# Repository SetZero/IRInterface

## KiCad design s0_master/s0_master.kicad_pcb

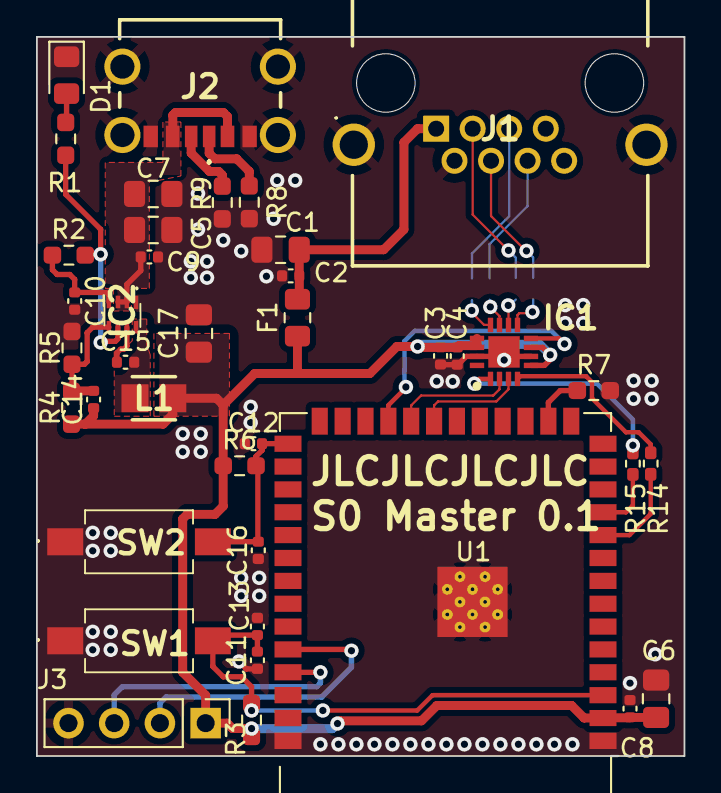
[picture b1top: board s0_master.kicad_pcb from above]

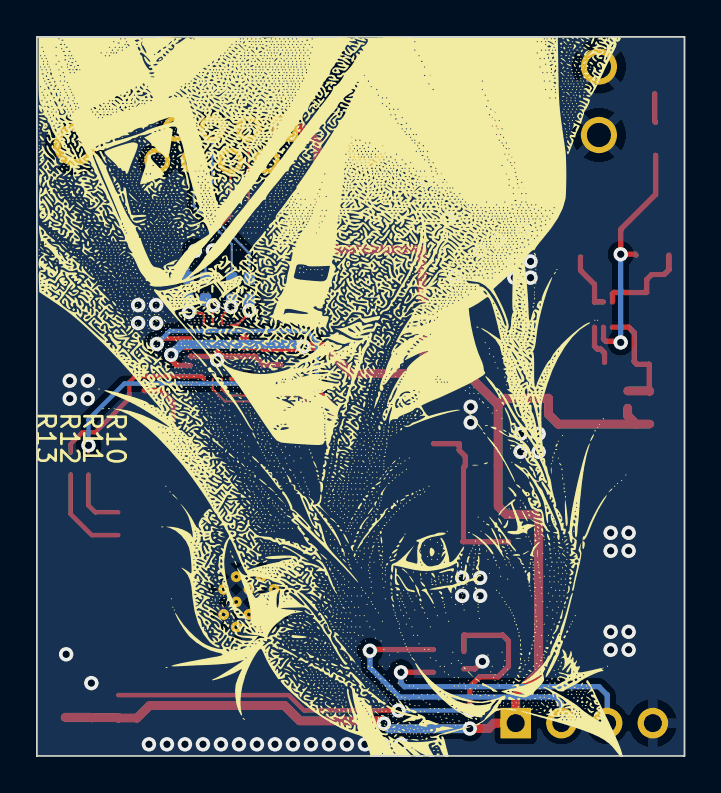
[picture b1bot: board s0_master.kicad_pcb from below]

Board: 2 copper layers, 36.0 x 40.0 mm, 43 parts (4 on the bottom side), 32 nets.

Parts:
C1: 100u; C_0805_2012Metric_Pad1.18x1.45mm_HandSolder
C2, C3, C4: 1u; C_0402_1005Metric
C5, C7: 10uF; C_0805_2012Metric_Pad1.18x1.45mm_HandSolder
C6, C17: 22uF; C_0805_2012Metric_Pad1.18x1.45mm_HandSolder
C8, C9, C11, C12, C13, C15, C16: 0.1uF; C_0402_1005Metric
C10: 1uF; C_0402_1005Metric
C14: 22pF; C_0402_1005Metric
D1: LED_Small; LED_0805_2012Metric_Pad1.15x1.40mm_HandSolder
F1: 1A; Fuse_0805_2012Metric_Pad1.15x1.40mm_HandSolder
IC1: THVD1424RGTR; QFN50P300X300X100-17N-D
IC2: MP2322GQH-Z; MP2322GQHZ
J1: RJHSE5E80
J2: 217175-0001; 2171750001
J3: DEBUG; PinHeader_1x04_P2.54mm_Vertical
L1: 3.3uH; INDPM2424X100N
R1: 75R; R_0603_1608Metric_Pad0.98x0.95mm_HandSolder
R2: 100k; R_0603_1608Metric_Pad0.98x0.95mm_HandSolder
R3, R6, R8, R9: 10k; R_0603_1608Metric_Pad0.98x0.95mm_HandSolder
R4: 976k; R_0603_1608Metric_Pad0.98x0.95mm_HandSolder
R5: 220k; R_0603_1608Metric_Pad0.98x0.95mm_HandSolder
R7: 2k; R_0603_1608Metric_Pad0.98x0.95mm_HandSolder
R10, R11, R12, R13, R14, R15: 0R; R_0402_1005Metric_Pad0.72x0.64mm_HandSolder
SW1, SW2: SW_Omron_B3FS; PTS636SP50SMTRLFS
U1: ESP32-S3-WROOM-1

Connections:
+3V3: C3.1, C4.1, C6.2, C8.2, C14.1, C17.1, F1.1, IC1.5 (TERM_TX), IC1.7 (TERM_RX), IC1.13 (VIO), IC1.14 (VCC), J3.1, L1.2, R3.1, R4.1, R6.1, U1.2 (3V3)
+5V: C5.1, C7.1, C9.1, IC2.2 (IN), IC2.3 (EN), J2.A9 (VBUS_1), J2.B9 (VBUS_2)
BOOT: C12.2, C16.2, R6.2, SW2.2, U1.27 (GPIO0/BOOT)
DI+: J1.4, R13.1
DI-: J1.3, R12.2
DO+: J1.5, R10.2
DO-: J1.6, R11.2
EN: C11.2, C13.2, R3.2, SW1.2, U1.3 (EN)
GND: C1.2, C2.2, C3.2, C4.2, C5.2, C6.1, C7.2, C8.1, C9.2, C10.2, C11.1, C12.1, C13.1, C16.1, C17.2, D1.1 (K), IC1.6 (GND), IC1.15 (H/~F), IC1.17 (EP), IC2.1 (GND), J1.2, J1.MH1, J1.MH2, J2.A12 (GND_1), J2.B12 (GND_2), J2.MH1, J2.MH2, J2.MH3, J2.MH4, J3.4, R5.2, R7.2, R8.2, R9.2, SW1.1, SW2.1, U1.1 (GND), U1.40 (GND), U1.41 (GND)
GPIO46: R7.1, U1.16 (GPIO46)
unnamed: D1.2 (A), R1.2
unnamed: IC1.12 (A), R10.1
unnamed: IC1.11 (B), R11.1
unnamed: IC1.4 (D), R14.2
unnamed: IC1.1 (R), R15.1
unnamed: IC1.9 (Y), R13.2
unnamed: IC1.10 (Z), R12.1
unnamed: C15.1, IC2.7 (BST)
unnamed: C14.2, IC2.5 (FB), R4.2, R5.1
unnamed: IC2.6 (PG), R1.1, R2.2
unnamed: C15.2, IC2.8 (SW), L1.1
unnamed: C10.1, IC2.4 (VCC), R2.1
unnamed: J2.A5 (CC1), R8.1
unnamed: J2.B5 (CC2), R9.1
RXD0: J3.2, U1.36 (U0RXD/GPIO44/CLK_OUT2)
SLR: IC1.8 (SLR), U1.23 (GPIO21)
TXD0: J3.3, U1.37 (U0TXD/GPIO43/CLK_OUT1)
UART2_DE: IC1.3 (DE), U1.21 (GPIO13/TOUCH13/ADC2_CH2/FSPIQ/FSPIIO7/S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)
UART2_RE: IC1.2 (~RE), U1.22 (GPIO14/TOUCH14/ADC2_CH3/FSPIWP/FSPIDQS/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)
UART2_RX: R15.2, U1.11 (GPIO18/U1RXD/ADC2_CH7/CLK_OUT3)
UART2_TX: R14.1, U1.10 (GPIO17/U1TXD/ADC2_CH6)
VIN: C1.1, C2.1, F1.2, J1.1

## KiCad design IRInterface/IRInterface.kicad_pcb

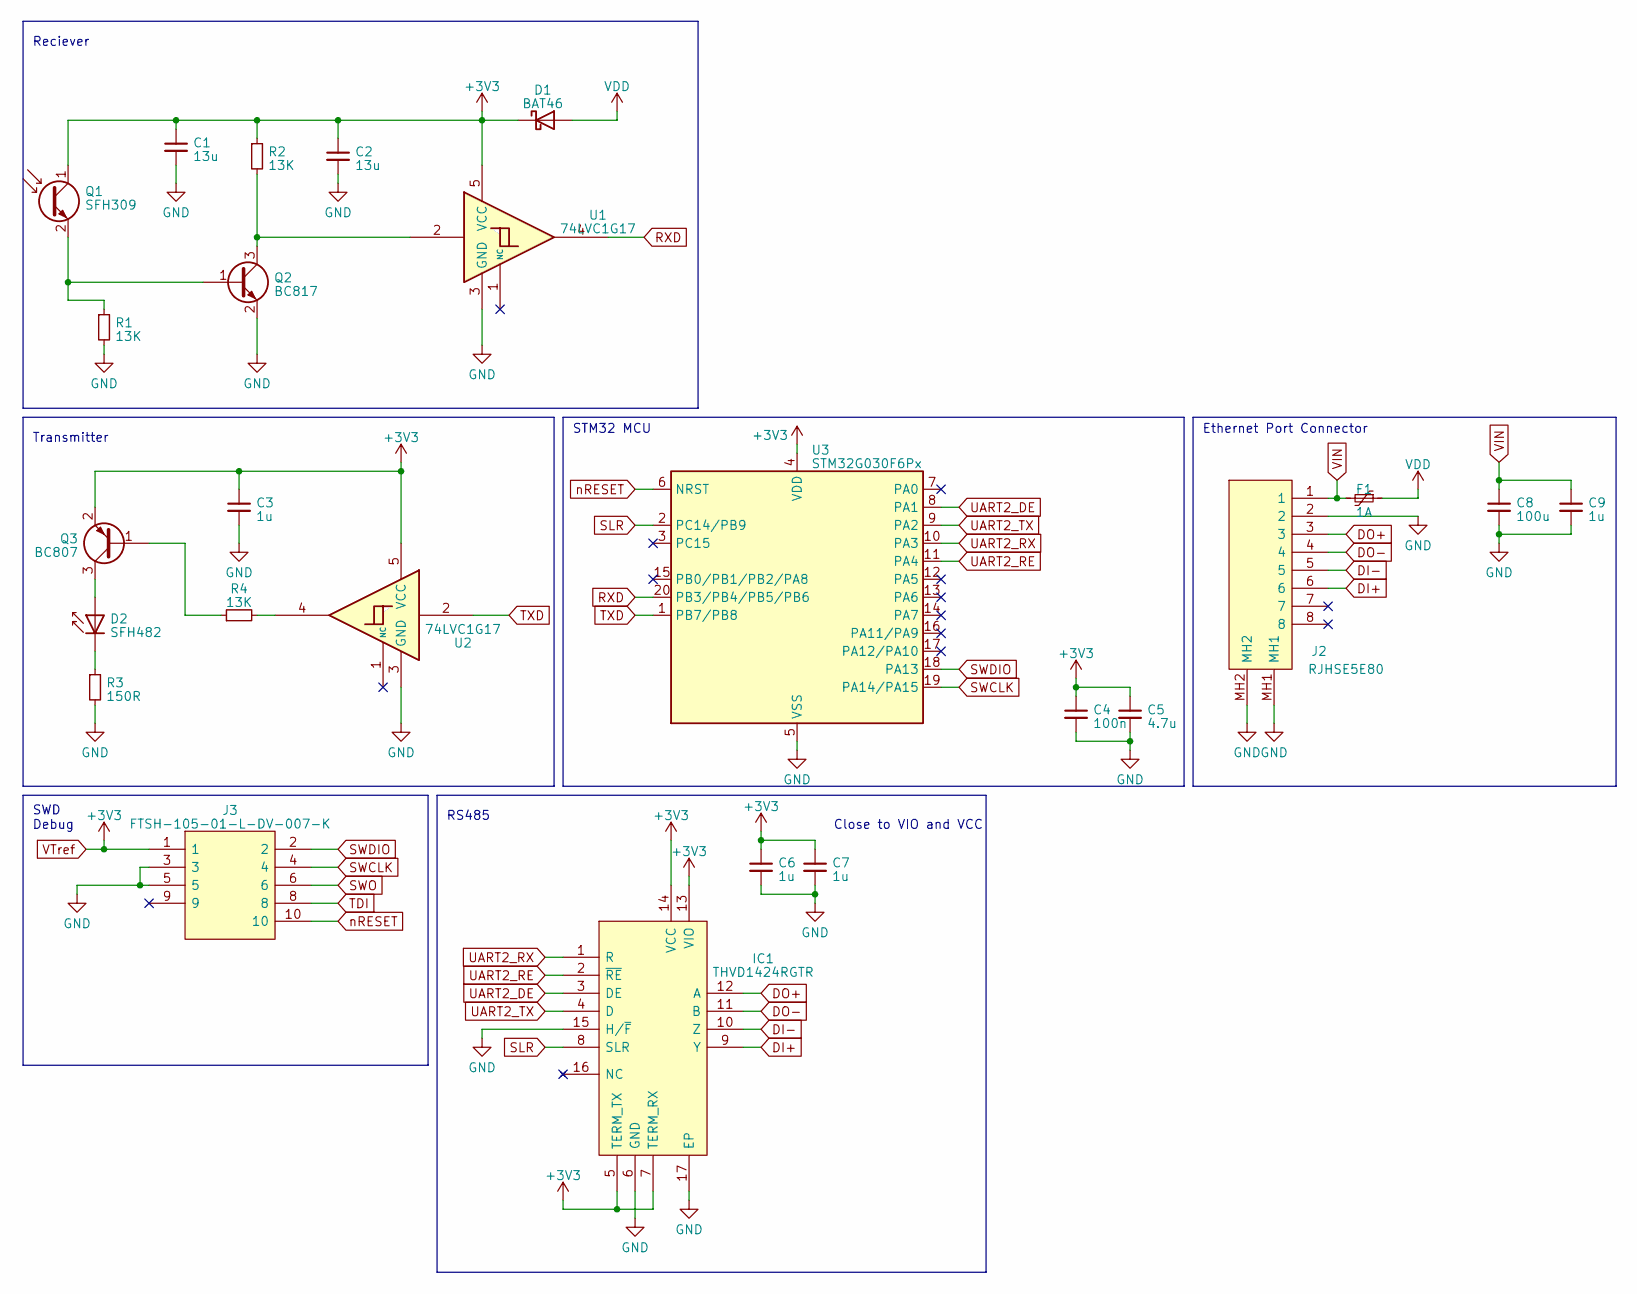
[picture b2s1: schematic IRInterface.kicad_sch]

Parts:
C1, C2: 13u; C_0402_1005Metric
C3, C6, C7, C9: 1u; C_0402_1005Metric
C4: 100n; C_0402_1005Metric
C5: 4.7u; C_0402_1005Metric
C8: 100u; C_0805_2012Metric_Pad1.18x1.45mm_HandSolder
D1: BAT46; D_SOD-123F
D2: SFH482; TO-18-2_Window
F1: 1A; Fuse_0805_2012Metric_Pad1.15x1.40mm_HandSolder
IC1: THVD1424RGTR; QFN50P300X300X100-17N-D; Mouser Part Number 595-THVD1424RGTR
J2: RJHSE5E80; Mouser Part Number 523-RJHSE5E80
J3: FTSH-105-01-L-DV-007-K; FTSH10501LDV007K; Mouser Part Number 200-FTSH10501LDV007K
Q1: SFH309; SFH309FA4
Q2: BC817; SOT-23
Q3: BC807; SOT-23-3
R1, R2, R4: 13K; R_0402_1005Metric_Pad0.72x0.64mm_HandSolder
R3: 150R; R_0402_1005Metric_Pad0.72x0.64mm_HandSolder
U1, U2: 74LVC1G17; SOT95P280X145-5N
U3: STM32G030F6Px; TSSOP-20_4.4x6.5mm_P0.65mm

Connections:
DI+: IC1.9 (Y), J2.6
DI-: IC1.10 (Z), J2.5
DO+: IC1.12 (A), J2.3
DO-: IC1.11 (B), J2.4
GND: C1.2, C2.2, C3.2, C4.2, C5.2, C6.2, C7.2, C8.2, C9.2, IC1.6 (GND), IC1.15 (H/~F), IC1.17 (EP), J2.2, J2.MH1, J2.MH2, J3.3, J3.5, Q2.2 (E), R1.2, R3.2, U1.3 (GND), U2.3 (GND), U3.5 (VSS)
unnamed: D2.2 (A), Q3.3 (C)
unnamed: D2.1 (K), R3.1
unnamed: Q1.2 (E), Q2.1 (B), R1.1
unnamed: Q2.3 (C), R2.2, U1.2
unnamed: Q3.1 (B), R4.1
unnamed: R4.2, U2.4
RXD: U1.4, U3.20 (PB3/PB4/PB5/PB6)
SLR: IC1.8 (SLR), U3.2 (PC14/PB9)
SWCLK: J3.4, U3.19 (PA14/PA15)
SWDIO: J3.2, U3.18 (PA13)
SWO: J3.6
TDI: J3.8
TXD: U2.2, U3.1 (PB7/PB8)
UART2_DE: IC1.3 (DE), U3.8 (PA1)
UART2_RE: IC1.2 (~RE), U3.11 (PA4)
UART2_RX: IC1.1 (R), U3.10 (PA3)
UART2_TX: IC1.4 (D), U3.9 (PA2)
VDD: D1.2 (A), F1.1
VIN: C8.1, C9.1, F1.2, J2.1
VTref: C1.1, C2.1, C3.1, C4.1, C5.1, C6.1, C7.1, D1.1 (K), IC1.5 (TERM_TX), IC1.7 (TERM_RX), IC1.13 (VIO), IC1.14 (VCC), J3.1, Q1.1 (C), Q3.2 (E), R2.1, U1.5 (VCC), U2.5 (VCC), U3.4 (VDD)
nRESET: J3.10, U3.6 (NRST)

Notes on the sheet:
Ethernet Port Connector
Close to VIO and VCC
SWD Debug
RS485
Reciever
Transmitter
STM32 MCU

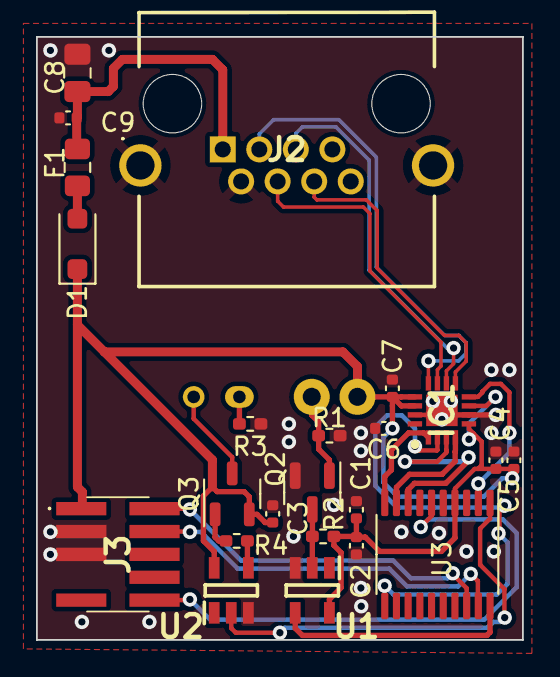
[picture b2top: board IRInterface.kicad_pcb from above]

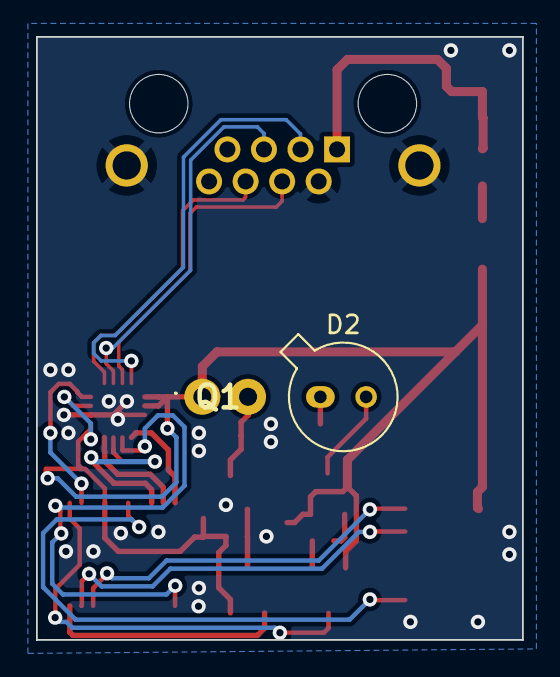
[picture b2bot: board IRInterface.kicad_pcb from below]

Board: 2 copper layers, 27.0 x 33.5 mm, 25 parts (2 on the bottom side), 24 nets.

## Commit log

2023-04-08 Added Initial IR Interface Project Files
2023-04-08 Added Symbol libraries and restructure schematic
2023-04-08 Fix review findings
2023-04-08 layout review
2023-04-12 Added S0 Master Layout
